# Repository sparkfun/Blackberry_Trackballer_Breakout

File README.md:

**NOTE:** *This product has been retired from our catalog. If you are looking for more up-to-date info, please check out some of these resources to see how other users are still hacking and improving on this product.*
* *[SparkFun Forum](https://forum.sparkfun.com/)*
* *[Comments Here on GitHub](https://github.com/sparkfun/Blackberry_Trackballer_Breakout/issues)*
* *[IRC Channel](https://www.sparkfun.com/news/263)*

SparkFun BlackBerry Trackballer Breakout
========================================

[*SparkFun BlackBerry Trackballer Breakout (COM-13169)*](https://www.sparkfun.com/products/13169)

The SparkFun BlackBerry Trackballer Breakout gives you easy access to a trackball which measures up, down, left, and right movements, clicks on the board, as well as adding a bit of flair to your project with four built-in LEDs. The trackballer breakout can be hooked into an Arduino compatible device to provide you with an intuitive direction controller.

Repository Contents
-------------------
 
* **/Firmware** - Example Arduino code 
* **/Hardware** - Eagle design files (.brd, .sch) for the main PCB, and the mounting PCB. 
* **/Production** - Production panel files (.brd) for the main PCB. The mounting PCB did not need to be panelized. 

Documentation
--------------
* **[Hookup Guide](https://learn.sparkfun.com/tutorials/blackberry-trackballer-breakout-hookup-guide)** - Basic hookup guide for the Trackballer Breakout.
* **[SparkFun Fritzing repo](https://github.com/sparkfun/Fritzing_Parts)** - Fritzing diagrams for SparkFun products.
* **[SparkFun 3D Model repo](https://github.com/sparkfun/3D_Models)** - 3D models of SparkFun products. 

Product Versions
----------------
* [COM-13169](https://www.sparkfun.com/products/13169)- Version 1.3. Retired.
* [COM-09320](https://www.sparkfun.com/products/9320)- Version 1.2. Retired. 

License Information
-------------------
This product is _**open source**_! 

The **hardware** is released under [Creative Commons ShareAlike 4.0 International](https://creativecommons.org/licenses/by-sa/4.0/).

The **code** is beerware; if you see me (or any other SparkFun employee) at the local, and you've found our code helpful, please buy us a round!

Please use, reuse, and modify these files as you see fit. Please maintain attribution to SparkFun Electronics and release anything derivative under the same license.

Distributed as-is; no warranty is given.

- Your friends at SparkFun.

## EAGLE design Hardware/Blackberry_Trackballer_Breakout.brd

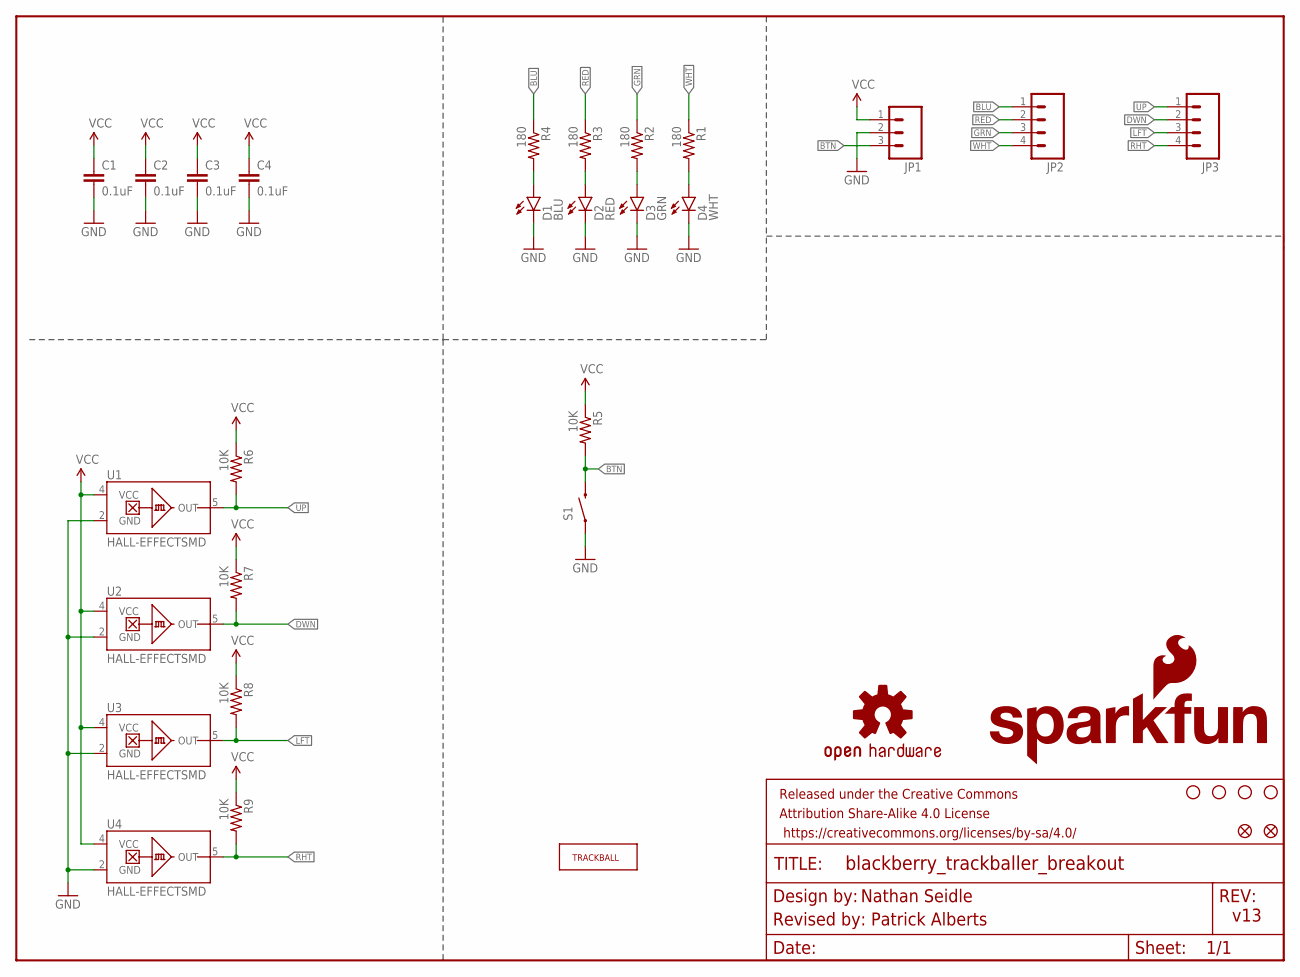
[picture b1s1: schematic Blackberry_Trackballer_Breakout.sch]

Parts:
C1, C2, C3, C4: 0.1uF; 0603-CAP
D1: BLU; LED-0603
D2: RED; LED-0603
D3: GRN; LED-0603
D4: WHT; LED-0603
E$1, E$2: FIDUCIAL1X2; FIDUCIAL-1X2
FRAME1: FRAME-LETTER; CREATIVE_COMMONS
JP1: M03PTH; 1X03
JP2, JP3: M04PTH; 1X04
LOGO1: SFE_LOGO_NAME_FLAME.2_INCH; SFE_LOGO_NAME_FLAME_.2
LOGO2: OSHW-LOGOS; OSHW-LOGO-S
R1, R2, R3, R4: 180; 0603-RES
R5, R6, R7, R8, R9: 10K; 0603-RES
S1: SWITCH-MOMENTARY-2SMD-2; TACTILE_SWITCH_SMD-2
U1, U2, U3, U4: HALL-EFFECTSMD; SC70
U$1, U$8, U$11, U$14: STAND-OFF
U$3: TRACKBALLMECH; TRACKBALL

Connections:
BLU: JP2.1, R4.1
BTN: JP1.3, R5.2, S1.1 (2)
DWN: JP3.2, R7.2, U2.5 (OUT)
GND: C1.2, C2.2, C3.2, C4.2, D1.C, D2.C, D3.C, D4.C, JP1.2, S1.2 (1), U1.2 (GND), U2.2 (GND), U3.2 (GND), U4.2 (GND)
GRN: JP2.3, R2.1
LFT: JP3.3, R8.2, U3.5 (OUT)
unnamed: D3.A, R2.2
unnamed: D2.A, R3.2
unnamed: D1.A, R4.2
unnamed: D4.A, R1.2
RED: JP2.2, R3.1
RHT: JP3.4, R9.2, U4.5 (OUT)
UP: JP3.1, R6.2, U1.5 (OUT)
VCC: C1.1, C2.1, C3.1, C4.1, JP1.1, R5.1, R6.1, R7.1, R8.1, R9.1, U1.4 (VCC), U2.4 (VCC), U3.4 (VCC), U4.4 (VCC)
WHT: JP2.4, R1.1

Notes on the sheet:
v13
Nathan Seidle
Revised by: Patrick Alberts

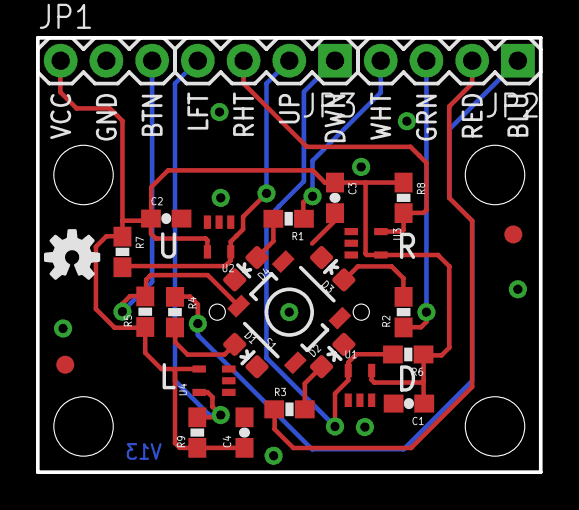
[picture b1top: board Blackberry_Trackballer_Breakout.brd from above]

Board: 2 copper layers, 27.9 x 24.1 mm, 35 parts (1 on the bottom side), 15 nets.

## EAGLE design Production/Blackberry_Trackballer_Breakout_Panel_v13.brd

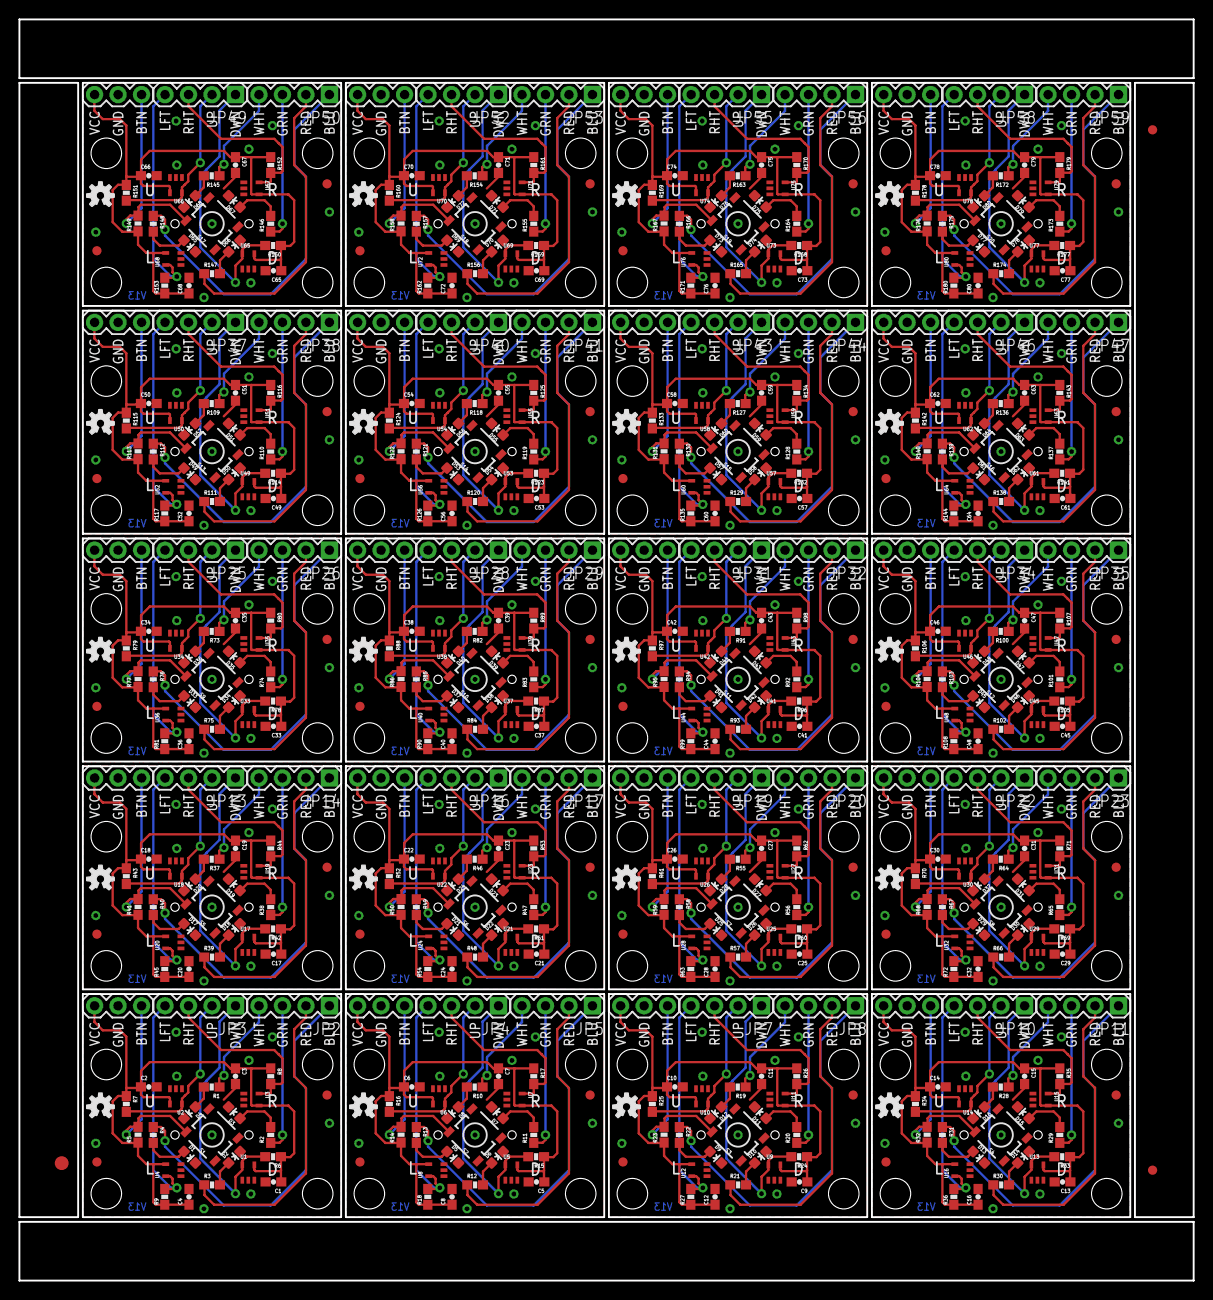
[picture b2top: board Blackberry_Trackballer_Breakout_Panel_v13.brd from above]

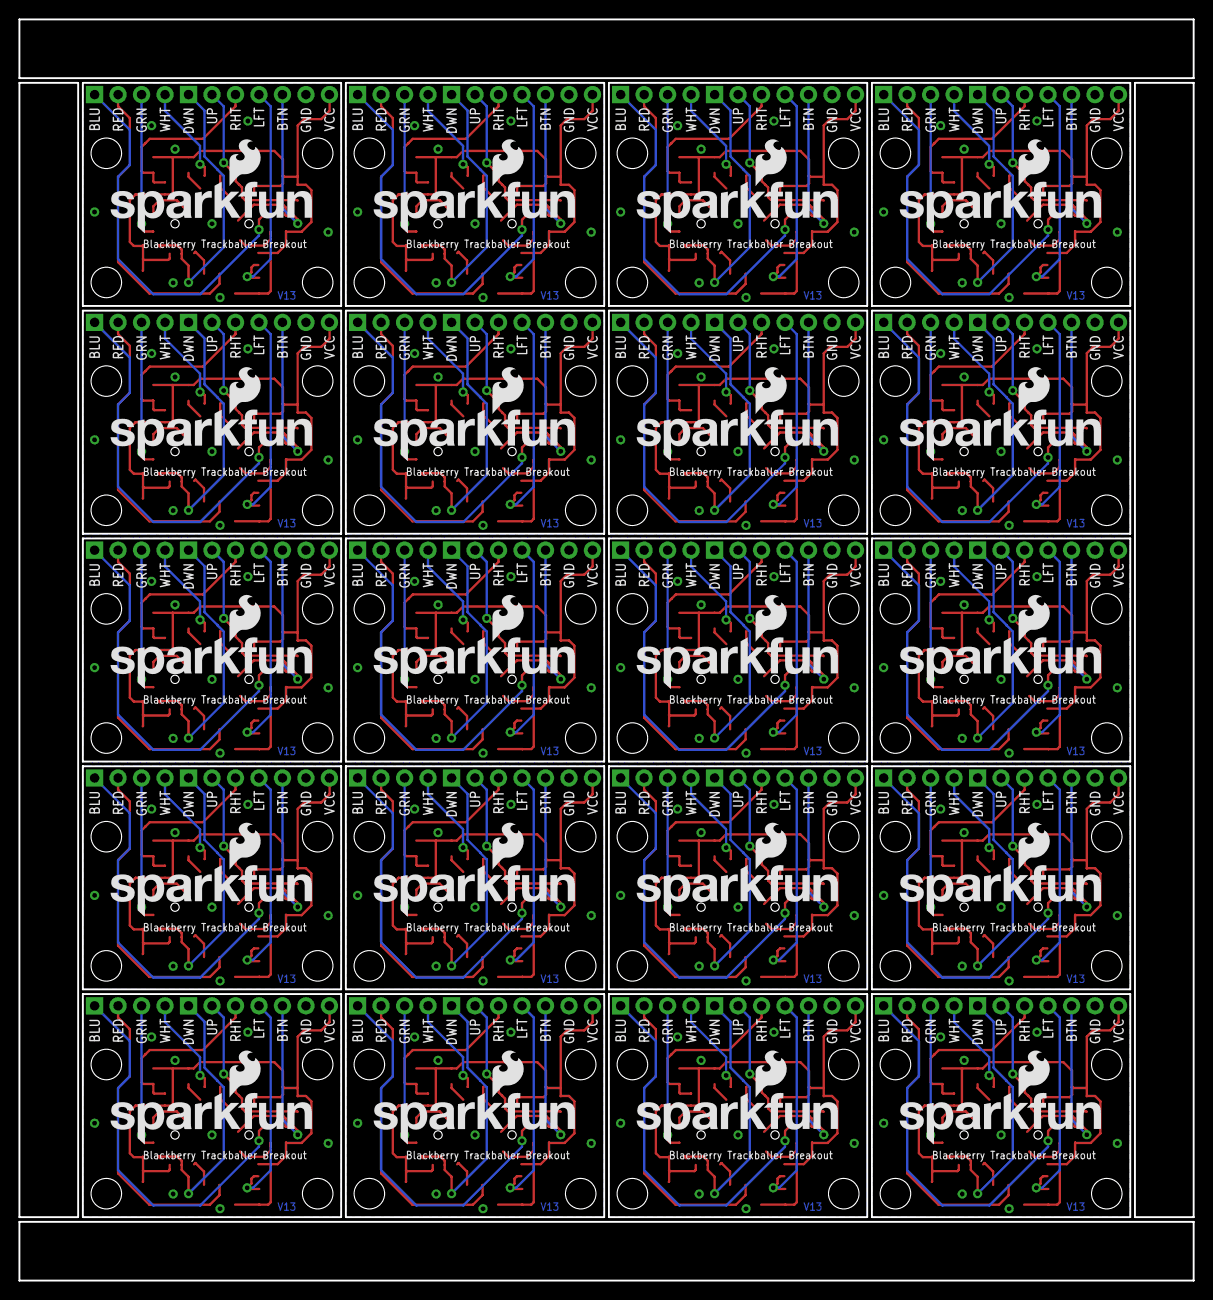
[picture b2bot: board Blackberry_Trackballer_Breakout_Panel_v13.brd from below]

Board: 2 copper layers, 127.0 x 136.4 mm, 683 parts (20 on the bottom side), 300 nets.

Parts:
C1, C2, C3, C4, C5, C6, C7, C8, C9, C10, C11, C12, C13, C14, C15, C16, C17, C18, C19, C20, C21, C22, C23, C24, C25, C26, C27, C28, C29, C30, C31, C32, C33, C34, C35, C36, C37, C38, C39, C40, C41, C42, C43, C44, C45, C46, C47, C48, C49, C50, C51, C52, C53, C54, C55, C56, C57, C58, C59, C60, C61, C62, C63, C64, C65, C66, C67, C68, C69, C70, C71, C72, C73, C74, C75, C76, C77, C78, C79, C80: 0.1uF; 0603-CAP
D1, D5, D9, D13, D17, D21, D25, D29, D33, D37, D41, D45, D49, D53, D57, D61, D65, D69, D73, D77: BLU; LED-0603
D2, D6, D10, D14, D18, D22, D26, D30, D34, D38, D42, D46, D50, D54, D58, D62, D66, D70, D74, D78: RED; LED-0603
D3, D7, D11, D15, D19, D23, D27, D31, D35, D39, D43, D47, D51, D55, D59, D63, D67, D71, D75, D79: GRN; LED-0603
D4, D8, D12, D16, D20, D24, D28, D32, D36, D40, D44, D48, D52, D56, D60, D64, D68, D72, D76, D80: WHT; LED-0603
E$1, E$2, E$3, E$4, E$5, E$6, E$7, E$8, E$9, E$10, E$11, E$12, E$13, E$14, E$15, E$16, E$17, E$18, E$19, E$20, E$21, E$22, E$23, E$24, E$25, E$26, E$27, E$28, E$29, E$30, E$31, E$32, E$33, E$34, E$35, E$36, E$37, E$38, E$39, E$40: FIDUCIAL1X2; FIDUCIAL-1X2
E$41: FIDUCIAL-1.5X3
E$44, E$45: FIDUCIAL-1X2
JP1, JP6, JP9, JP12, JP15, JP18, JP21, JP24, JP27, JP30, JP33, JP36, JP39, JP42, JP45, JP48, JP51, JP54, JP57, JP60: 1X03
JP2, JP3, JP4, JP5, JP7, JP8, JP10, JP11, JP13, JP14, JP16, JP17, JP19, JP20, JP22, JP23, JP25, JP26, JP28, JP29, JP31, JP32, JP34, JP35, JP37, JP38, JP40, JP41, JP43, JP44, JP46, JP47, JP49, JP50, JP52, JP53, JP55, JP56, JP58, JP59: 1X04
LOGO1, LOGO3, LOGO5, LOGO7, LOGO9, LOGO11, LOGO13, LOGO15, LOGO17, LOGO19, LOGO21, LOGO23, LOGO25, LOGO27, LOGO29, LOGO31, LOGO33, LOGO35, LOGO37, LOGO39: SFE_LOGO_NAME_FLAME.2_INCH; SFE_LOGO_NAME_FLAME_.2
LOGO2, LOGO4, LOGO6, LOGO8, LOGO10, LOGO12, LOGO14, LOGO16, LOGO18, LOGO20, LOGO22, LOGO24, LOGO26, LOGO28, LOGO30, LOGO32, LOGO34, LOGO36, LOGO38, LOGO40: OSHW-LOGOS; OSHW-LOGO-S
R1, R2, R3, R4, R10, R11, R12, R13, R19, R20, R21, R22, R28, R29, R30, R31, R37, R38, R39, R40, R46, R47, R48, R49, R55, R56, R57, R58, R64, R65, R66, R67, R73, R74, R75, R76, R82, R83, R84, R85, R91, R92, R93, R94, R100, R101, R102, R103, R109, R110, R111, R112, R118, R119, R120, R121, R127, R128, R129, R130, R136, R137, R138, R139, R145, R146, R147, R148, R154, R155, R156, R157, R163, R164, R165, R166, R172, R173, R174, R175: 180; 0603-RES
R5, R6, R7, R8, R9, R14, R15, R16, R17, R18, R23, R24, R25, R26, R27, R32, R33, R34, R35, R36, R41, R42, R43, R44, R45, R50, R51, R52, R53, R54, R59, R60, R61, R62, R63, R68, R69, R70, R71, R72, R77, R78, R79, R80, R81, R86, R87, R88, R89, R90, R95, R96, R97, R98, R99, R104, R105, R106, R107, R108, R113, R114, R115, R116, R117, R122, R123, R124, R125, R126, R131, R132, R133, R134, R135, R140, R141, R142, R143, R144, R149, R150, R151, R152, R153, R158, R159, R160, R161, R162, R167, R168, R169, R170, R171, R176, R177, R178, R179, R180: 10K; 0603-RES
S1, S2, S3, S4, S5, S6, S7, S8, S9, S10, S11, S12, S13, S14, S15, S16, S17, S18, S19, S20: SWITCH-MOMENTARY-2SMD-2; TACTILE_SWITCH_SMD-2
U1, U2, U3, U4, U5, U6, U7, U8, U9, U10, U11, U12, U13, U14, U15, U16, U17, U18, U19, U20, U21, U22, U23, U24, U25, U26, U27, U28, U29, U30, U31, U32, U33, U34, U35, U36, U37, U38, U39, U40, U41, U42, U43, U44, U45, U46, U47, U48, U49, U50, U51, U52, U53, U54, U55, U56, U57, U58, U59, U60, U61, U62, U63, U64, U65, U66, U67, U68, U69, U70, U71, U72, U73, U74, U75, U76, U77, U78, U79, U80: HALL-EFFECTSMD; SC70
U$1, U$2, U$4, U$5, U$6, U$8, U$9, U$10, U$11, U$12, U$13, U$14, U$16, U$17, U$18, U$19, U$21, U$22, U$23, U$24, U$26, U$27, U$28, U$29, U$31, U$32, U$33, U$34, U$36, U$37, U$38, U$39, U$41, U$42, U$43, U$44, U$46, U$47, U$48, U$49, U$51, U$52, U$53, U$54, U$56, U$57, U$58, U$59, U$61, U$62, U$63, U$64, U$66, U$67, U$68, U$69, U$71, U$72, U$73, U$74, U$76, U$77, U$78, U$79, U$81, U$82, U$83, U$84, U$86, U$87, U$88, U$89, U$91, U$92, U$93, U$94, U$96, U$97, U$98, U$99: STAND-OFF
U$3, U$7, U$15, U$20, U$25, U$30, U$35, U$40, U$45, U$50, U$55, U$60, U$65, U$70, U$75, U$80, U$85, U$90, U$95, U$100: TRACKBALLMECH; TRACKBALL

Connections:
BLU: JP2.1, R4.1
BLU1: JP5.1, R13.1
BLU2: JP8.1, R22.1
BLU3: JP11.1, R31.1
BLU4: JP14.1, R40.1
BLU5: JP17.1, R49.1
BLU6: JP20.1, R58.1
BLU7: JP23.1, R67.1
BLU8: JP26.1, R76.1
BLU9: JP29.1, R85.1
BLU10: JP32.1, R94.1
BLU11: JP35.1, R103.1
BLU12: JP38.1, R112.1
BLU13: JP41.1, R121.1
BLU14: JP44.1, R130.1
BLU15: JP47.1, R139.1
BLU16: JP50.1, R148.1
BLU17: JP53.1, R157.1
BLU18: JP56.1, R166.1
BLU19: JP59.1, R175.1
BTN: JP1.3, R5.2, S1.1
BTN1: JP6.3, R14.2, S2.1
BTN2: JP9.3, R23.2, S3.1
BTN3: JP12.3, R32.2, S4.1
BTN4: JP15.3, R41.2, S5.1
BTN5: JP18.3, R50.2, S6.1
BTN6: JP21.3, R59.2, S7.1
BTN7: JP24.3, R68.2, S8.1
BTN8: JP27.3, R77.2, S9.1
BTN9: JP30.3, R86.2, S10.1
BTN10: JP33.3, R95.2, S11.1
BTN11: JP36.3, R104.2, S12.1
BTN12: JP39.3, R113.2, S13.1
BTN13: JP42.3, R122.2, S14.1
BTN14: JP45.3, R131.2, S15.1
BTN15: JP48.3, R140.2, S16.1
BTN16: JP51.3, R149.2, S17.1
BTN17: JP54.3, R158.2, S18.1
BTN18: JP57.3, R167.2, S19.1
BTN19: JP60.3, R176.2, S20.1
DWN: JP3.2, R7.2, U2.5
DWN1: JP4.2, R16.2, U6.5
DWN2: JP7.2, R25.2, U10.5
DWN3: JP10.2, R34.2, U14.5
DWN4: JP13.2, R43.2, U18.5
DWN5: JP16.2, R52.2, U22.5
DWN6: JP19.2, R61.2, U26.5
DWN7: JP22.2, R70.2, U30.5
DWN8: JP25.2, R79.2, U34.5
DWN9: JP28.2, R88.2, U38.5
DWN10: JP31.2, R97.2, U42.5
DWN11: JP34.2, R106.2, U46.5
DWN12: JP37.2, R115.2, U50.5
DWN13: JP40.2, R124.2, U54.5
DWN14: JP43.2, R133.2, U58.5
DWN15: JP46.2, R142.2, U62.5
DWN16: JP49.2, R151.2, U66.5
DWN17: JP52.2, R160.2, U70.5
DWN18: JP55.2, R169.2, U74.5
DWN19: JP58.2, R178.2, U78.5
GND: C1.2, C2.2, C3.2, C4.2, D1.C, D2.C, D3.C, D4.C, JP1.2, S1.2, U1.2, U2.2, U3.2, U4.2
GND1: C5.2, C6.2, C7.2, C8.2, D5.C, D6.C, D7.C, D8.C, JP6.2, S2.2, U5.2, U6.2, U7.2, U8.2
GND2: C9.2, C10.2, C11.2, C12.2, D9.C, D10.C, D11.C, D12.C, JP9.2, S3.2, U9.2, U10.2, U11.2, U12.2
GND3: C13.2, C14.2, C15.2, C16.2, D13.C, D14.C, D15.C, D16.C, JP12.2, S4.2, U13.2, U14.2, U15.2, U16.2
GND4: C17.2, C18.2, C19.2, C20.2, D17.C, D18.C, D19.C, D20.C, JP15.2, S5.2, U17.2, U18.2, U19.2, U20.2
GND5: C21.2, C22.2, C23.2, C24.2, D21.C, D22.C, D23.C, D24.C, JP18.2, S6.2, U21.2, U22.2, U23.2, U24.2
GND6: C25.2, C26.2, C27.2, C28.2, D25.C, D26.C, D27.C, D28.C, JP21.2, S7.2, U25.2, U26.2, U27.2, U28.2
GND7: C29.2, C30.2, C31.2, C32.2, D29.C, D30.C, D31.C, D32.C, JP24.2, S8.2, U29.2, U30.2, U31.2, U32.2
GND8: C33.2, C34.2, C35.2, C36.2, D33.C, D34.C, D35.C, D36.C, JP27.2, S9.2, U33.2, U34.2, U35.2, U36.2
GND9: C37.2, C38.2, C39.2, C40.2, D37.C, D38.C, D39.C, D40.C, JP30.2, S10.2, U37.2, U38.2, U39.2, U40.2
GND10: C41.2, C42.2, C43.2, C44.2, D41.C, D42.C, D43.C, D44.C, JP33.2, S11.2, U41.2, U42.2, U43.2, U44.2
GND11: C45.2, C46.2, C47.2, C48.2, D45.C, D46.C, D47.C, D48.C, JP36.2, S12.2, U45.2, U46.2, U47.2, U48.2
GND12: C49.2, C50.2, C51.2, C52.2, D49.C, D50.C, D51.C, D52.C, JP39.2, S13.2, U49.2, U50.2, U51.2, U52.2
GND13: C53.2, C54.2, C55.2, C56.2, D53.C, D54.C, D55.C, D56.C, JP42.2, S14.2, U53.2, U54.2, U55.2, U56.2
GND14: C57.2, C58.2, C59.2, C60.2, D57.C, D58.C, D59.C, D60.C, JP45.2, S15.2, U57.2, U58.2, U59.2, U60.2
GND15: C61.2, C62.2, C63.2, C64.2, D61.C, D62.C, D63.C, D64.C, JP48.2, S16.2, U61.2, U62.2, U63.2, U64.2
GND16: C65.2, C66.2, C67.2, C68.2, D65.C, D66.C, D67.C, D68.C, JP51.2, S17.2, U65.2, U66.2, U67.2, U68.2
GND17: C69.2, C70.2, C71.2, C72.2, D69.C, D70.C, D71.C, D72.C, JP54.2, S18.2, U69.2, U70.2, U71.2, U72.2
GND18: C73.2, C74.2, C75.2, C76.2, D73.C, D74.C, D75.C, D76.C, JP57.2, S19.2, U73.2, U74.2, U75.2, U76.2
GND19: C77.2, C78.2, C79.2, C80.2, D77.C, D78.C, D79.C, D80.C, JP60.2, S20.2, U77.2, U78.2, U79.2, U80.2
GRN: JP2.3, R2.1
GRN1: JP5.3, R11.1
GRN2: JP8.3, R20.1
GRN3: JP11.3, R29.1
GRN4: JP14.3, R38.1
GRN5: JP17.3, R47.1
GRN6: JP20.3, R56.1
GRN7: JP23.3, R65.1
GRN8: JP26.3, R74.1
GRN9: JP29.3, R83.1
GRN10: JP32.3, R92.1
GRN11: JP35.3, R101.1
GRN12: JP38.3, R110.1
GRN13: JP41.3, R119.1
GRN14: JP44.3, R128.1
GRN15: JP47.3, R137.1
GRN16: JP50.3, R146.1
GRN17: JP53.3, R155.1
GRN18: JP56.3, R164.1
GRN19: JP59.3, R173.1
LFT: JP3.3, R8.2, U3.5
LFT1: JP4.3, R17.2, U7.5
LFT2: JP7.3, R26.2, U11.5
LFT3: JP10.3, R35.2, U15.5
LFT4: JP13.3, R44.2, U19.5
LFT5: JP16.3, R53.2, U23.5
LFT6: JP19.3, R62.2, U27.5
LFT7: JP22.3, R71.2, U31.5
LFT8: JP25.3, R80.2, U35.5
LFT9: JP28.3, R89.2, U39.5
LFT10: JP31.3, R98.2, U43.5
LFT11: JP34.3, R107.2, U47.5
LFT12: JP37.3, R116.2, U51.5
LFT13: JP40.3, R125.2, U55.5
LFT14: JP43.3, R134.2, U59.5
LFT15: JP46.3, R143.2, U63.5
LFT16: JP49.3, R152.2, U67.5
LFT17: JP52.3, R161.2, U71.5
LFT18: JP55.3, R170.2, U75.5
LFT19: JP58.3, R179.2, U79.5
unnamed: D3.A, R2.2
unnamed: D2.A, R3.2
unnamed: D1.A, R4.2
unnamed: D4.A, R1.2
unnamed: D7.A, R11.2
unnamed: D6.A, R12.2
unnamed: D5.A, R13.2
unnamed: D8.A, R10.2
unnamed: D11.A, R20.2
unnamed: D10.A, R21.2
unnamed: D9.A, R22.2
unnamed: D12.A, R19.2
unnamed: D15.A, R29.2
unnamed: D14.A, R30.2
unnamed: D13.A, R31.2
unnamed: D16.A, R28.2
unnamed: D19.A, R38.2
unnamed: D18.A, R39.2
unnamed: D17.A, R40.2
unnamed: D20.A, R37.2
unnamed: D23.A, R47.2
unnamed: D22.A, R48.2
unnamed: D21.A, R49.2
unnamed: D24.A, R46.2
unnamed: D27.A, R56.2
unnamed: D26.A, R57.2
unnamed: D25.A, R58.2
unnamed: D28.A, R55.2
unnamed: D31.A, R65.2
unnamed: D30.A, R66.2
unnamed: D29.A, R67.2
unnamed: D32.A, R64.2
unnamed: D35.A, R74.2
unnamed: D34.A, R75.2
unnamed: D33.A, R76.2
unnamed: D36.A, R73.2
unnamed: D39.A, R83.2
unnamed: D38.A, R84.2
unnamed: D37.A, R85.2
unnamed: D40.A, R82.2
unnamed: D43.A, R92.2
unnamed: D42.A, R93.2
unnamed: D41.A, R94.2
unnamed: D44.A, R91.2
unnamed: D47.A, R101.2
unnamed: D46.A, R102.2
unnamed: D45.A, R103.2
unnamed: D48.A, R100.2
unnamed: D51.A, R110.2
unnamed: D50.A, R111.2
unnamed: D49.A, R112.2
unnamed: D52.A, R109.2
unnamed: D55.A, R119.2
unnamed: D54.A, R120.2
unnamed: D53.A, R121.2
unnamed: D56.A, R118.2
unnamed: D59.A, R128.2
unnamed: D58.A, R129.2
unnamed: D57.A, R130.2
unnamed: D60.A, R127.2
unnamed: D63.A, R137.2
unnamed: D62.A, R138.2
unnamed: D61.A, R139.2
unnamed: D64.A, R136.2
unnamed: D67.A, R146.2
unnamed: D66.A, R147.2
unnamed: D65.A, R148.2
unnamed: D68.A, R145.2
unnamed: D71.A, R155.2
unnamed: D70.A, R156.2
unnamed: D69.A, R157.2
unnamed: D72.A, R154.2
unnamed: D75.A, R164.2
unnamed: D74.A, R165.2
unnamed: D73.A, R166.2
unnamed: D76.A, R163.2
unnamed: D79.A, R173.2
unnamed: D78.A, R174.2
unnamed: D77.A, R175.2
unnamed: D80.A, R172.2
RED: JP2.2, R3.1
RED1: JP5.2, R12.1
RED2: JP8.2, R21.1
RED3: JP11.2, R30.1
RED4: JP14.2, R39.1
RED5: JP17.2, R48.1
RED6: JP20.2, R57.1
RED7: JP23.2, R66.1
RED8: JP26.2, R75.1
RED9: JP29.2, R84.1
RED10: JP32.2, R93.1
RED11: JP35.2, R102.1
RED12: JP38.2, R111.1
RED13: JP41.2, R120.1
RED14: JP44.2, R129.1
RED15: JP47.2, R138.1
RED16: JP50.2, R147.1
RED17: JP53.2, R156.1
RED18: JP56.2, R165.1
RED19: JP59.2, R174.1
RHT: JP3.4, R9.2, U4.5
RHT1: JP4.4, R18.2, U8.5
RHT2: JP7.4, R27.2, U12.5
RHT3: JP10.4, R36.2, U16.5
RHT4: JP13.4, R45.2, U20.5
RHT5: JP16.4, R54.2, U24.5
RHT6: JP19.4, R63.2, U28.5
RHT7: JP22.4, R72.2, U32.5
RHT8: JP25.4, R81.2, U36.5
RHT9: JP28.4, R90.2, U40.5
RHT10: JP31.4, R99.2, U44.5
RHT11: JP34.4, R108.2, U48.5
RHT12: JP37.4, R117.2, U52.5
RHT13: JP40.4, R126.2, U56.5
RHT14: JP43.4, R135.2, U60.5
RHT15: JP46.4, R144.2, U64.5
RHT16: JP49.4, R153.2, U68.5
RHT17: JP52.4, R162.2, U72.5
RHT18: JP55.4, R171.2, U76.5
RHT19: JP58.4, R180.2, U80.5
UP: JP3.1, R6.2, U1.5
UP1: JP4.1, R15.2, U5.5
UP2: JP7.1, R24.2, U9.5
UP3: JP10.1, R33.2, U13.5
UP4: JP13.1, R42.2, U17.5
UP5: JP16.1, R51.2, U21.5
UP6: JP19.1, R60.2, U25.5
UP7: JP22.1, R69.2, U29.5
UP8: JP25.1, R78.2, U33.5
UP9: JP28.1, R87.2, U37.5
UP10: JP31.1, R96.2, U41.5
UP11: JP34.1, R105.2, U45.5
UP12: JP37.1, R114.2, U49.5
UP13: JP40.1, R123.2, U53.5
UP14: JP43.1, R132.2, U57.5
UP15: JP46.1, R141.2, U61.5
UP16: JP49.1, R150.2, U65.5
UP17: JP52.1, R159.2, U69.5
UP18: JP55.1, R168.2, U73.5
UP19: JP58.1, R177.2, U77.5
VCC: C1.1, C2.1, C3.1, C4.1, JP1.1, R5.1, R6.1, R7.1, R8.1, R9.1, U1.4, U2.4, U3.4, U4.4
VCC1: C5.1, C6.1, C7.1, C8.1, JP6.1, R14.1, R15.1, R16.1, R17.1, R18.1, U5.4, U6.4, U7.4, U8.4
VCC2: C9.1, C10.1, C11.1, C12.1, JP9.1, R23.1, R24.1, R25.1, R26.1, R27.1, U9.4, U10.4, U11.4, U12.4
VCC3: C13.1, C14.1, C15.1, C16.1, JP12.1, R32.1, R33.1, R34.1, R35.1, R36.1, U13.4, U14.4, U15.4, U16.4
VCC4: C17.1, C18.1, C19.1, C20.1, JP15.1, R41.1, R42.1, R43.1, R44.1, R45.1, U17.4, U18.4, U19.4, U20.4
VCC5: C21.1, C22.1, C23.1, C24.1, JP18.1, R50.1, R51.1, R52.1, R53.1, R54.1, U21.4, U22.4, U23.4, U24.4
VCC6: C25.1, C26.1, C27.1, C28.1, JP21.1, R59.1, R60.1, R61.1, R62.1, R63.1, U25.4, U26.4, U27.4, U28.4
VCC7: C29.1, C30.1, C31.1, C32.1, JP24.1, R68.1, R69.1, R70.1, R71.1, R72.1, U29.4, U30.4, U31.4, U32.4
VCC8: C33.1, C34.1, C35.1, C36.1, JP27.1, R77.1, R78.1, R79.1, R80.1, R81.1, U33.4, U34.4, U35.4, U36.4
VCC9: C37.1, C38.1, C39.1, C40.1, JP30.1, R86.1, R87.1, R88.1, R89.1, R90.1, U37.4, U38.4, U39.4, U40.4
VCC10: C41.1, C42.1, C43.1, C44.1, JP33.1, R95.1, R96.1, R97.1, R98.1, R99.1, U41.4, U42.4, U43.4, U44.4
VCC11: C45.1, C46.1, C47.1, C48.1, JP36.1, R104.1, R105.1, R106.1, R107.1, R108.1, U45.4, U46.4, U47.4, U48.4
VCC12: C49.1, C50.1, C51.1, C52.1, JP39.1, R113.1, R114.1, R115.1, R116.1, R117.1, U49.4, U50.4, U51.4, U52.4
VCC13: C53.1, C54.1, C55.1, C56.1, JP42.1, R122.1, R123.1, R124.1, R125.1, R126.1, U53.4, U54.4, U55.4, U56.4
VCC14: C57.1, C58.1, C59.1, C60.1, JP45.1, R131.1, R132.1, R133.1, R134.1, R135.1, U57.4, U58.4, U59.4, U60.4
VCC15: C61.1, C62.1, C63.1, C64.1, JP48.1, R140.1, R141.1, R142.1, R143.1, R144.1, U61.4, U62.4, U63.4, U64.4
VCC16: C65.1, C66.1, C67.1, C68.1, JP51.1, R149.1, R150.1, R151.1, R152.1, R153.1, U65.4, U66.4, U67.4, U68.4
VCC17: C69.1, C70.1, C71.1, C72.1, JP54.1, R158.1, R159.1, R160.1, R161.1, R162.1, U69.4, U70.4, U71.4, U72.4
VCC18: C73.1, C74.1, C75.1, C76.1, JP57.1, R167.1, R168.1, R169.1, R170.1, R171.1, U73.4, U74.4, U75.4, U76.4
VCC19: C77.1, C78.1, C79.1, C80.1, JP60.1, R176.1, R177.1, R178.1, R179.1, R180.1, U77.4, U78.4, U79.4, U80.4
WHT: JP2.4, R1.1
WHT1: JP5.4, R10.1
WHT2: JP8.4, R19.1
WHT3: JP11.4, R28.1
WHT4: JP14.4, R37.1
WHT5: JP17.4, R46.1
WHT6: JP20.4, R55.1
WHT7: JP23.4, R64.1
WHT8: JP26.4, R73.1
WHT9: JP29.4, R82.1
WHT10: JP32.4, R91.1
WHT11: JP35.4, R100.1
WHT12: JP38.4, R109.1
WHT13: JP41.4, R118.1
WHT14: JP44.4, R127.1
WHT15: JP47.4, R136.1
WHT16: JP50.4, R145.1
WHT17: JP53.4, R154.1
WHT18: JP56.4, R163.1
WHT19: JP59.4, R172.1

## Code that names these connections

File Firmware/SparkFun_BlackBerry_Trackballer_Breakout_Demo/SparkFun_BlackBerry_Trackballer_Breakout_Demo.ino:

/**************************************************************************
SparkFun BlackBerry Trackballer Breakout Demo
Toni Klopfenstein @ SparkFun Electronics
March 2015
https://github.com/sparkfun/Blackberry_Trackballer_Breakout
This demo shows all the basic functionality of the SparkFun BlackBerry Trackballer Breakout (https://www.sparkfun.com/products/13169).
Development environment specifics:
Developed in Arduino 1.6.0
This code is beerware; if you see me (or any other SparkFun employee) at the local, and you've found our code helpful, please buy us a round!
Distributed as-is; no warranty is given.
***************************************************************************/

//Define Trackballer Breakout pin connections to Arduino
#define Btn 2
#define Lft 3
#define Rht 4
#define Up 5
#define Dwn 6
#define WHT_LED 7
#define GRN_LED 8
#define RED_LED 9
#define BLU_LED 10

//Define variables used in sketch
int buttonClick;
unsigned long mouse_Lft;
unsigned long mouse_Rht;
unsigned long mouse_Up;
unsigned long mouse_Dwn;
int x_position;
int y_position;

/*********************Setup Loop*************************/
void setup() {
  
  //Define pin functionality on the Arduino
  pinMode(Btn, INPUT);
  pinMode(Lft, INPUT);
  pinMode(Rht, INPUT);
  pinMode(Up, INPUT);
  pinMode(Dwn, INPUT);
  pinMode(WHT_LED, OUTPUT);
  pinMode(GRN_LED, OUTPUT);
  pinMode(RED_LED, OUTPUT);
  pinMode(BLU_LED, OUTPUT);
  
  //Pull LED pins low to prevent flickering
  digitalWrite(WHT_LED, LOW);
  digitalWrite(GRN_LED, LOW);
  digitalWrite(RED_LED, LOW);
  digitalWrite(BLU_LED, LOW);
  
  //Start Serial port for debugging. 
  Serial.begin(9600); 
  Serial.println("Begin Trackballer Demo");
 
  //Demo each LED by turning them on individually for one second. 
  Serial.println("Turn on LEDs individually");
  digitalWrite(WHT_LED, HIGH);
  delay(1000);
  digitalWrite(WHT_LED, LOW);
  
  digitalWrite(GRN_LED, HIGH);
  delay(1000);
  digitalWrite(GRN_LED, LOW);
  
  digitalWrite(RED_LED, HIGH);
  delay(1000);
  digitalWrite(RED_LED, LOW);
  
  digitalWrite(BLU_LED, HIGH);
  delay(1000);
  digitalWrite(BLU_LED, LOW);
  
  Serial.println("Begin Trackball tracking");
}


/*********************Main Loop*************************/
void loop() {
  
  //Wait for 2ms on each direction pin for movement.
  //Pins are driven HIGH by the breakout board.
  //pulseIn measures the length of each pulse in microseconds. 
  mouse_Lft = pulseIn(Lft, HIGH, 20000);
  mouse_Rht = pulseIn(Rht, HIGH, 20000);
  mouse_Up = pulseIn(Up, HIGH, 20000);
  mouse_Dwn = pulseIn(Dwn, HIGH, 20000);
  
  //Determine if there was movement in any direction. 
  //If movement occurred, adjust x/y coordinates based on movements.
  //Directionality is based off of an x/y plane (i.e., Up 1 unit and Right 1 unit = (1,1))
  if (mouse_Lft > 0)
  {
    x_position= --x_position;
  }
  if (mouse_Rht > 0)
  {
    x_position= ++x_position;
  }
  if (mouse_Up > 0)
  {
    y_position= ++y_position;
  }
  if (mouse_Dwn > 0)
  {
    y_position= --y_position;
  }
  
  //Output x/y coordinates to Serial terminal
  Serial.print("Trackball Position: \t X-Position= ");  
  Serial.print(x_position);
  Serial.print(" \t Y-position= ");
  Serial.print(y_position);
  Serial.println();
  
  //Check for button click. If present, print to Serial monitor.
  buttonClick = digitalRead(Btn);
  if (buttonClick == LOW)
  {
    Serial.println("Click");  
  }
}

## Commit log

2014-10-14 Initial Commit
    initial commit with brd/sch
2014-10-29 0603, sch update, top layer
    Updated all components to 0603
    Updated the sche to frame letter
    added rev code
    made second pcb to secure the trackball and rid the pcb of glue.
2014-12-08 initial qc checklist changes.
2014-12-10 Schematic Clean up, added Blackberry device...
    and trace re routes.
2014-12-10 Added attributes to swch, trackball and whte led
2014-12-10 Initial commit of the brd/sch files.
2014-12-10 Added version #
2014-12-10 Added vcc range to sch
2014-12-10 Adjusted bottom silk
    increased text ratio to 15% on product name text
    aligned header labels properly
    moved SFE logo to avoid overlap with header labels silk
2014-12-15 created panel v13
2014-12-16 Fixed silk error
2015-03-05 Adding .git* files
2015-03-05 Updating file names, directory names to prevent issues on different OS
2015-03-13 Initial firmware commit
2015-03-13 PulseIn sketch commit - WIP
2015-03-13 Coding in progress
2015-03-16 Testing Interrupt code/hookup
2015-03-16 Testing digitalPinToInterrupt-Does not work
2015-03-16 Final sketch commit, using pulseIn
2015-03-16 Fixing pin connections

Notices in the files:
parts and their libraries:
SparkFun-Capacitors: Licensing: Creative Commons ShareAlike 4.0 International - https://creativecommons.org/licenses/by-sa/4.0
SparkFun-Aesthetics: Released under the Creative Commons Attribution Share-Alike 4.0 License
SparkFun-Aesthetics: Released under the Creative Commons
